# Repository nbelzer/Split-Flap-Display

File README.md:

# Split Flap Display Firmware

Looking for support? Find help on discord ☝️

Firmware for the modular Split Flap Display created by [Morgan Manly](https://github.com/ManlyMorgan/Split-Flap-Display)

- [Instructables](https://www.instructables.com/Split-Flap-Display-3D-Printed-Modular-Compact-Encl/) ( Original )
- [Print Files](https://makerworld.com/en/models/1116618#profileId-1114192) ( Original, 37 characters version )
- [Print Files](https://makerworld.com/en/models/1296793-split-flap-display-extended-charset-48-flaps#profileId-1328346) ( Extended, 48 characters version )
- [Original firmware](https://github.com/ManlyMorgan/Split-Flap-Display)

## Features

- Fully 3D Printed Modular Split Flap Display with 37 or 48 Characters Per Module
- Small Size, 8 Modules are 320mm, 3 Modules are 130mm Wide. 80mm tall (original version) or 94mm (extended version) tall
- Fully configurable and controllable via Web Interface
    - Fetch display content from a configurable plain-text URL every minute
    - Configure WiFi, Timezone, and hardware settings
- MQTT Support
- OTA Firmware / Filesystem updating

## Supported boards

| Environment          | Processor     | Tested Boards                                                            |
| -------------------- | ------------- | ------------------------------------------------------------------------ |
| `esp32_c3` (default) | ESP32-C3FN4   | Teyleten Robot ESP32-C3-SuperMini<br>Waveshare ESP32-C3-Zero             |
| `esp32_s3`           | ESP32-S3FH4R2 | Waveshare ESP32-S3-Zero<sup>\*</sup><br>ESP32-S3 Super Mini<sup>\*</sup> |

<sub>\* Requires manually resetting the board into firmware upload mode by holding BOOT, pressing & releasing RESET, then releasing BOOT prior to upload. After uploading is successful, either press & release RESET or power cycle the board to put it in normal operation mode.</sub>

## Setup Instructions

1. Install dependencies
    - [PlatformIO Core CLI](https://platformio.org/install/cli)
    - [Node Version Mananger](https://github.com/nvm-sh/nvm)
    - [ClangFormat](https://clang.llvm.org/docs/ClangFormat.html) (Only required if contributing code)
1. [Download](https://github.com/jhoff/Split-Flap-Display/archive/refs/heads/main.zip) or clone this [git repository](https://github.com/jhoff/Split-Flap-Display).
1. Open a terminal and `cd` to the project root
1. Install required version of npm for the project - `nvm install`
1. Install build dependencies - `npm install`
1. Connect the ESP32 to your computer using a USB cable.
1. Build everything and upload to the board - `npm run build`

- Automatically formats all source code ( `npm run format` - if needed )
- Compiles and minifies all frontend assets ( `npm run assets` )
- Downloads all required arduino / esp32 libraries
- Compiles and uploads the esp32 firmware ( `npm run pio:firmware` or `pio run -t upload -e <environment>` )
- Compiles and uploads the littlefs filesystem ( `npm run pio:filesystem` or `pio run -t uploadfs -e <environment>` )

1. Enjoy!

### Using OTA to update the firmware

On the settings page set an OTA password to enable OTA updatable firmware. Use this same password for your `auth` flag in `platformio.ini`, and then use a device environment with `*_ota` appended (ie `esp32_s3_ota`) to upload a new firmware and/or filesystem

## Contributing

### Setup

1. Create a GitHub account if necessary and login.
1. [Fork](https://github.com/jhoff/Split-Flap-Display/fork) this repository.
1. Clone your forked repository to your local machine.

- `git clone https://github.com/your-username/Split-Flap-Display.git`

1. Install the dependencies listed in [Setup Instructions](#setup-instructions)
1. Skip step 2, complete the setup and use `npm run build` to test and upload your changes.

### Create your feature

1. Start a new branch with a descriptive name.
1. Compile and upload your changes

- `npm run pio:firmware` or `pio run -t upload -e <environment>` to compile firmware and upload
- `npm run pio:filesystem` or `pio run -t uploadfs -e <environment>` to compile the filesystem from `src/web` and upload
- You can do both together using `npm run pio` or `pio run -t upload -t uploadfs -e <environment>`

1. When ready, commit and push your changes to your forked repository.
1. Open a pull request to this repository.

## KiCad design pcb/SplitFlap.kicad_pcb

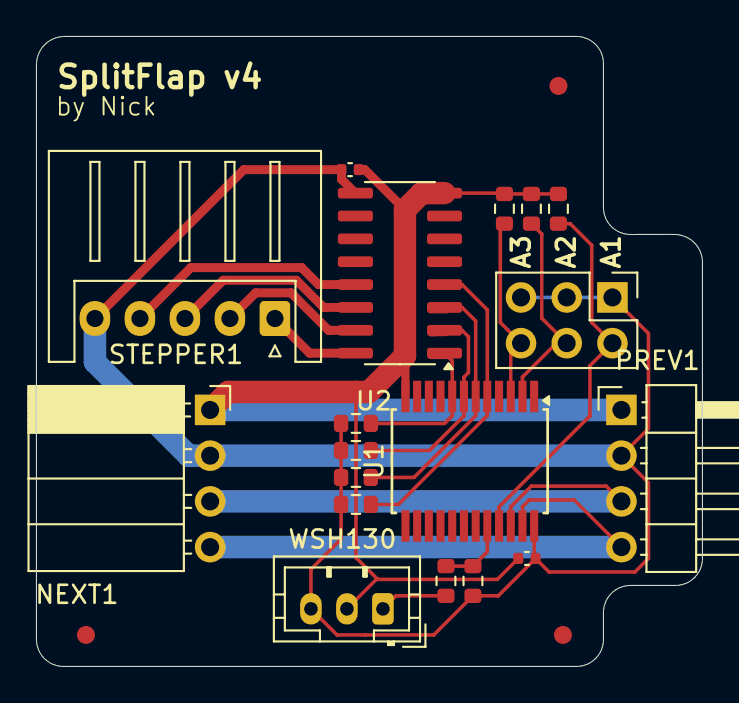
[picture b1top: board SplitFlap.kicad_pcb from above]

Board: 2 copper layers, 37.0 x 35.0 mm, 18 parts (0 on the bottom side), 17 nets.

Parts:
C1_BYPASS1, C2_BYPASS1: 0.1 µF; C_0402_1005Metric
J1: A1_3; PinHeader_2x03_P2.54mm_Vertical
NEXT1: Conn_01x04_Pin; PinSocket_1x04_P2.54mm_Horizontal
PREV1: Conn_01x04_Pin; PinHeader_1x04_P2.54mm_Horizontal
PULL_DOWN3, PULL_DOWN4, PULL_DOWN5: 47K; R_0603_1608Metric
PULL_UP2: 10K; R_0603_1608Metric
PULL_UP6, PULL_UP7, PULL_UP8, PULL_UP9: 10k; R_0603_1608Metric
SERIES1: 1k; R_0603_1608Metric
STEPPER1: Conn_01x05_Pin; JST_XH_S5B-XH-A_1x05_P2.50mm_Horizontal
U1: PCF8575DBR; SSOP-24_5.3x8.2mm_P0.65mm
U2: ULN2003; SOIC-16_3.9x9.9mm_P1.27mm
WSH130: Conn_01x03_Pin; JST_PH_B3B-PH-K_1x03_P2.00mm_Vertical

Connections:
+5V: C1_BYPASS1.1, C2_BYPASS1.2, J1.1, J1.3, J1.5, NEXT1.2, PREV1.2, PULL_UP2.1, PULL_UP6.1, PULL_UP7.1, PULL_UP8.1, PULL_UP9.1, STEPPER1.5, U1.24 (VCC), U2.9 (COM), WSH130.3
GND: C1_BYPASS1.2, C2_BYPASS1.1, NEXT1.1, PREV1.1, PULL_DOWN3.2, PULL_DOWN4.2, PULL_DOWN5.2, U1.12 (GND), U2.8 (GND), WSH130.2
unnamed: J1.2, PULL_DOWN5.1, U1.21 (A0)
unnamed: J1.4, PULL_DOWN4.1, U1.2 (A1)
unnamed: J1.6, PULL_DOWN3.1, U1.3 (A2)
unnamed: NEXT1.3, PREV1.3, U1.22 (SCL)
unnamed: NEXT1.4, PREV1.4, U1.23 (SDA)
unnamed: STEPPER1.1, U2.16 (O1)
unnamed: STEPPER1.2, U2.15 (O2)
unnamed: STEPPER1.3, U2.14 (O3)
unnamed: STEPPER1.4, U2.13 (O4)
unnamed: PULL_UP6.2, U1.5 (P1), U2.4 (I4)
unnamed: PULL_UP7.2, U1.6 (P2), U2.3 (I3)
unnamed: PULL_UP8.2, U1.7 (P3), U2.2 (I2)
unnamed: PULL_UP9.2, U1.8 (P4), U2.1 (I1)
unnamed: PULL_UP2.2, SERIES1.2, U1.20 (P17)
unnamed: SERIES1.1, WSH130.1

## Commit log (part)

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2025-04-30 Add 3.3v line for PCF8575
2025-05-07 Use two pin address connectors with pulldown resistor
2025-05-07 Replace linear regulator with AP2112K
    This regulator has a smaller footprint and seems to be better
    optimised for our use case (more efficient, lower idle power draw,
    less heat).
2025-05-07 Accomodate linear regulator and new address pins on PCB
2025-05-07 Add missing part numbers
2025-05-07 Minor pcb changes
    - Updates the position of the entire board down,
    - Adds an edge cut section for the WSH130 wiring.
    - Moves the ULN2003 up a bit to clean up the connections.
    - Updates silkscreen labels.
2025-05-07 Add missing part number for address pins
2025-05-15 Correct AP2112K capacitors
2025-05-28 Add pull-ups between PCF8575 and ULN2003
    This is necessary since the PCF8575 can only pull the output to 0, not
    bring it up to 3.3v, so a pull-up is necessary to communicate with the
    ULN2003 (which only responds to values 2.5v or above).
2025-06-03 Use 2x3 connector for address pins
    Saves on board space and component count
2025-06-03 Rewire PCB
2025-10-11 Eliminate 3.3v line from PCB
    Based on the findings by FoxManJ the 3.3v line is not required if we
    use a 4.7k Ohm pull-up to 5v for the SCL and SDA lines coming from the
    ESP32.
    By using this pull-up to 5V we eliminate the need for the PCF8575 to
    run at 3.3v to understand the signals from the ESP32, which was the
    reason I originally implemented the 3.3v line on each board.
2025-10-11 Use pinsocket and headers for board to board connector
    Eliminates the JST cables between boards.
2025-11-14 Update pin and header parts
2025-11-16 Add optional data lines pull-up
    Required as the ESP32 by default does not pull up the data lines to
    5v. Should only be activated once per circuit (display).
2025-11-16 Rename pull-up jumper
2026-02-09 Fix floating pull-ups
    The optional pull-ups added in v4 added an unintentional floating node
    that would tie SCL and SDA together whenever the pull-up pad was
    unsoldered. Causing the I2C bus to fail (surprisingly only after
    connecting 3 modules).
2026-02-10 Add fetch endpoint mode
2026-02-11 Update display to empty outside of working hours
2026-03-01 Remove pull-ups entirely
    For now manually soldering pull-ups to the ESP32 remain an easier solution.
2026-03-01 Extend PCB to 37mm
2026-03-01 Bump printed version number
